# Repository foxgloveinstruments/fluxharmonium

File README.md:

# fluxharmonium
hardware and software for the fluxharmonium

## Hardware

Hardware design files for the primary electronics are located in the `kicad` of each primary function; [conductor](hardware/conductor/kicad), [ensemble](hardware/ensemble/kicad/), and [output](hardware/output/kicad).

## Software

The embedded microcontroller is currently a [Pimoroni Tiny2040 8MB](https://shop.pimoroni.com/products/tiny-2040) running CircuitPython. Firmware for the controller is located in the [src folder](src/)

Tested with Adafruit CircuitPython 8.0.5 on 2023-03-31; Pimoroni Tiny 2040 (8MB) with rp2040

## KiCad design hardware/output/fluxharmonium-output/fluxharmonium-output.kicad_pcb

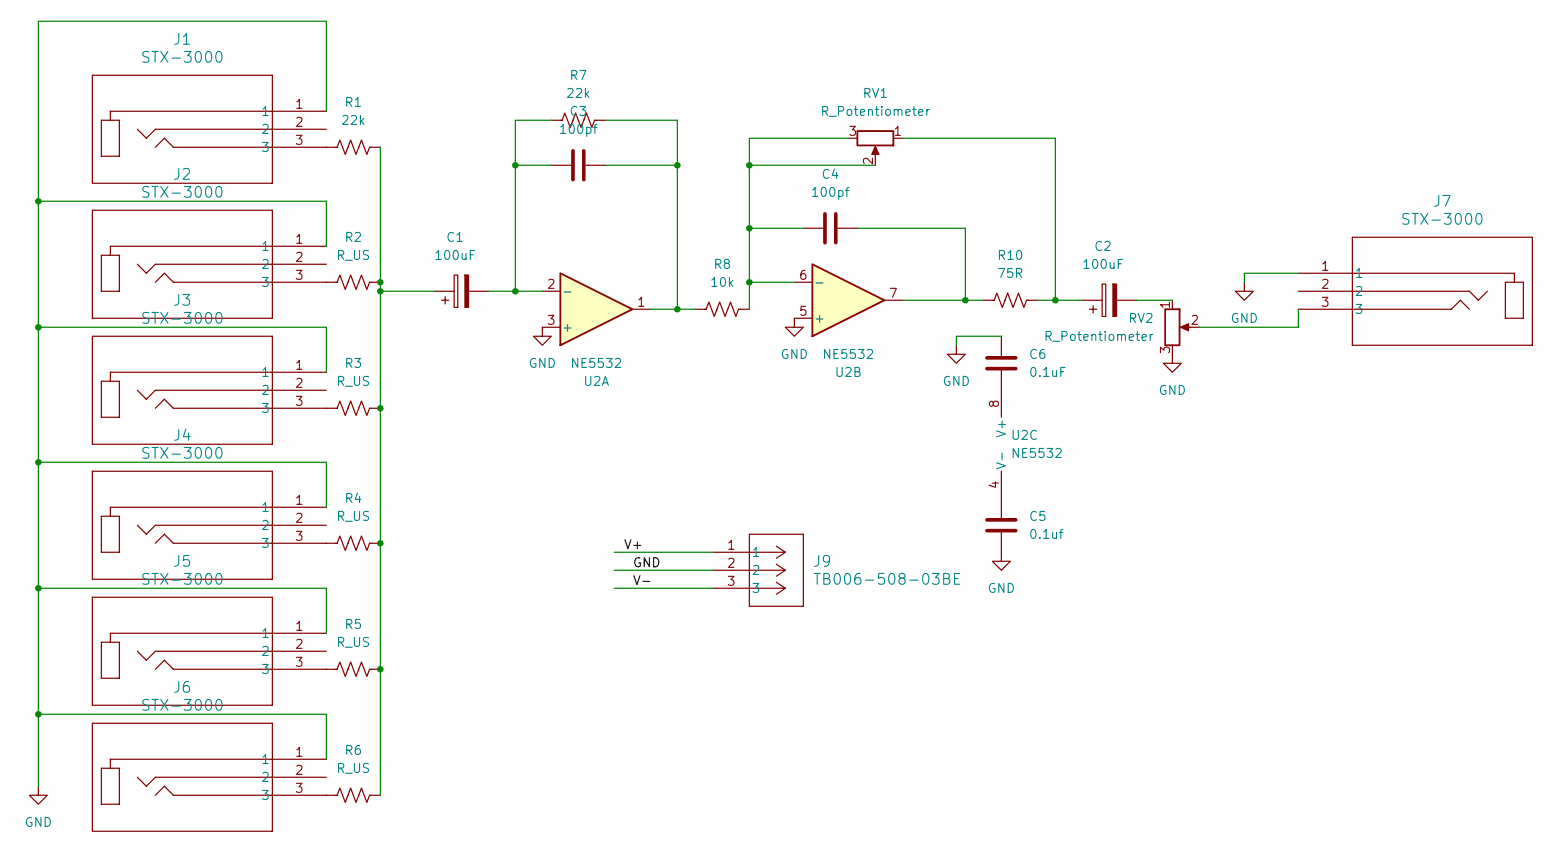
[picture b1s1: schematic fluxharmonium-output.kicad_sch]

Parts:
C1, C2: 100uF; CP_Radial_D5.0mm_P2.00mm
C3, C4: 100pf; C_Rect_L4.6mm_W2.0mm_P2.50mm_MKS02_FKP02
C5: 0.1uf; C_Disc_D3.8mm_W2.6mm_P2.50mm
C6: 0.1uF; C_Disc_D3.8mm_W2.6mm_P2.50mm
J1, J2, J3, J4, J5, J6, J7: STX-3000; STX-3000_KYC
J9: TB006-508-03BE; CONN3_TB006-508_CUD
R1, R7: 22k; R_Axial_DIN0207_L6.3mm_D2.5mm_P10.16mm_Horizontal
R2, R3, R4, R5, R6: R_US; R_Axial_DIN0207_L6.3mm_D2.5mm_P10.16mm_Horizontal
R8: 10k; R_Axial_DIN0207_L6.3mm_D2.5mm_P10.16mm_Horizontal
R10: 75R; R_Axial_DIN0207_L6.3mm_D2.5mm_P10.16mm_Horizontal
RV1: R_Potentiometer; Potentiometer_Bourns_3386P_Vertical
RV2: R_Potentiometer; PinSocket_1x03_P2.54mm_Vertical
U2: NE5532; DIP-8_W7.62mm

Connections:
/V+: J9.1
/V-: J9.3
GND: C5.1, C6.2, J1.1, J2.1, J3.1, J4.1, J5.1, J6.1, J7.1, J9.2, RV2.3, U2.3 (+), U2.5 (+)
unnamed: C1.1, R1.2, R2.2, R3.2, R4.2, R5.2, R6.2
unnamed: C2.1, R10.2, RV1.1
unnamed: C2.2, RV2.1
unnamed: C3.2, R7.2, R8.1, U2.1
unnamed: C4.2, R10.1, U2.7
unnamed: J1.3, R1.1
unnamed: J2.3, R2.1
unnamed: J3.3, R3.1
unnamed: J4.3, R4.1
unnamed: J5.3, R5.1
unnamed: J6.3, R6.1
unnamed: J7.3, RV2.2
unnamed: C1.2, C3.1, R7.1, U2.2 (-)
unnamed: C4.1, R8.2, RV1.2, RV1.3, U2.6 (-)
unnamed: C6.1, U2.8 (V+)
unnamed: C5.2, U2.4 (V-)

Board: 2 copper layers, 26 parts (0 on the bottom side), 17 nets, no tracks yet.

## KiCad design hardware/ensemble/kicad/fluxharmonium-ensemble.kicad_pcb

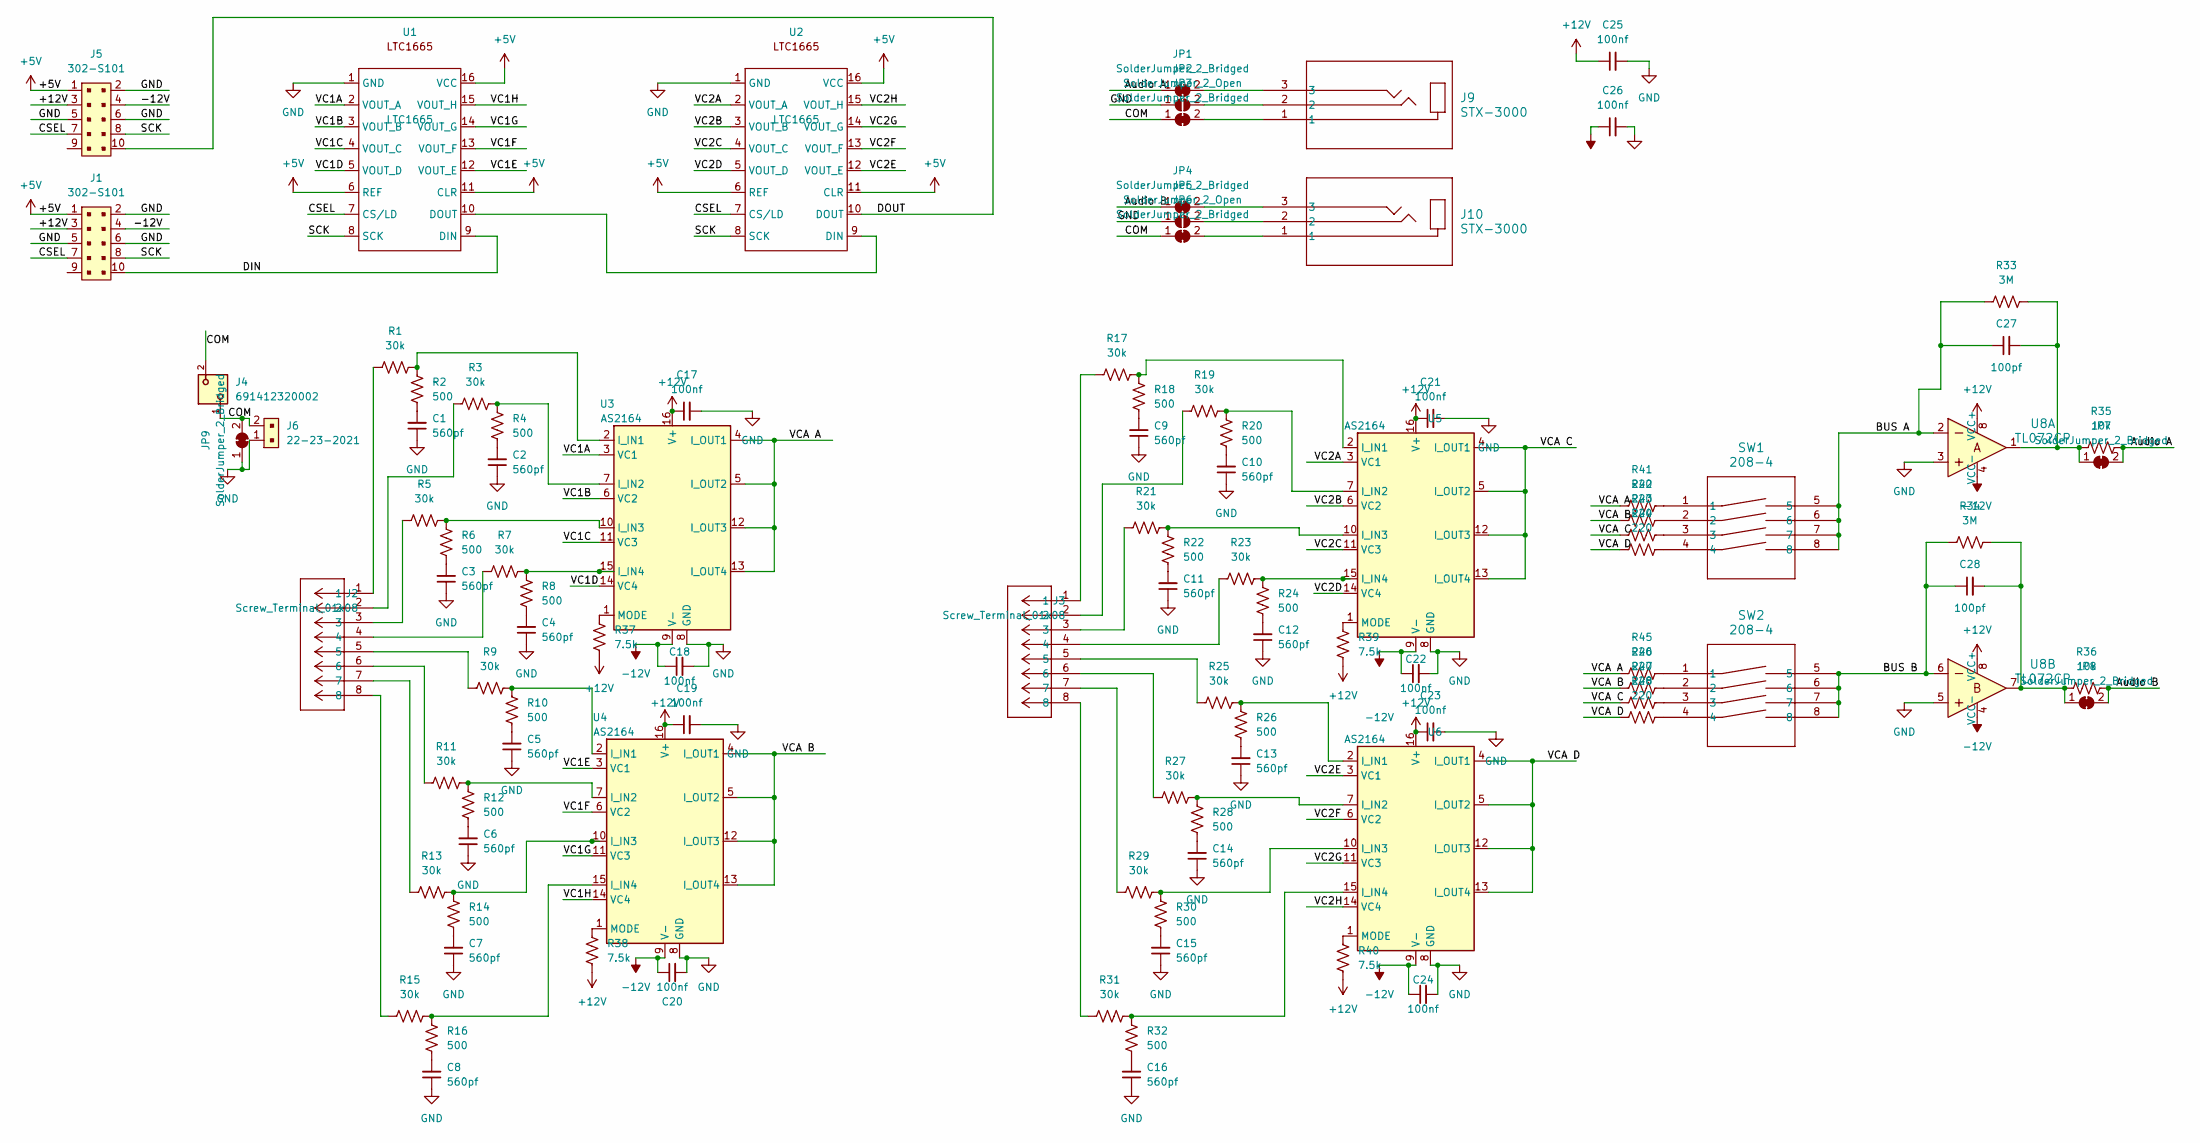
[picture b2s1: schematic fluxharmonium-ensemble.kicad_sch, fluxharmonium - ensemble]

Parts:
C1, C2, C3, C4, C5, C6, C7, C8, C9, C10, C11, C12, C13, C14, C15, C16: 560pf; C_Disc_D3.0mm_W2.0mm_P2.50mm
C17, C18, C19, C20, C21, C22, C23, C24, C25, C26: 100nf; C_Disc_D3.8mm_W2.6mm_P2.50mm
C27, C28: 100pf; C_Disc_D3.8mm_W2.6mm_P2.50mm
J1, J5: 302-S101; IDC-Header_2x05_P2.54mm_Latch_Vertical; MPN 302-S101; Digi-Key_PN ED1543-ND
J2, J3: Screw_Terminal_01x08; CONN_1755794_PXC
J4: 691412320002; PART-NUMBER 691412320002
J6: 22-23-2021; PinHeader_1x2_P2.54mm_Drill1.02mm; MPN 22-23-2021; Digi-Key_PN WM4200-ND
J9, J10: STX-3000; xess-STX-3000_KYC
JP1, JP3, JP4, JP6, JP7, JP8, JP9: SolderJumper_2_Bridged; SolderJumper-2_P1.3mm_Bridged_RoundedPad1.0x1.5mm
JP2, JP5: SolderJumper_2_Open; SolderJumper-2_P1.3mm_Open_RoundedPad1.0x1.5mm
R1, R3, R5, R7, R9, R11, R13, R15, R17, R19, R21, R23, R25, R27, R29, R31: 30k; R_Axial_DIN0207_L6.3mm_D2.5mm_P2.54mm_Vertical
R2, R4, R6, R8, R10, R12, R14, R16, R18, R20, R22, R24, R26, R28, R30, R32: 500; R_Axial_DIN0207_L6.3mm_D2.5mm_P2.54mm_Vertical
R33, R34: 3M; R_Axial_DIN0207_L6.3mm_D2.5mm_P2.54mm_Vertical
R35, R36: 10k; R_Axial_DIN0207_L6.3mm_D2.5mm_P2.54mm_Vertical
R37, R38, R39, R40: 7.5k; R_Axial_DIN0207_L6.3mm_D2.5mm_P2.54mm_Vertical
R41, R42, R43, R44, R45, R46, R47, R48: 220; R_Axial_DIN0207_L6.3mm_D2.5mm_P2.54mm_Vertical
SW1, SW2: 208-4; DIP8_208-4_CTS
U1, U2: LTC1665; DIP-16_W7.62mm_LongPads
U3, U4, U5, U6: AS2164; DIP-16_W7.62mm_LongPads
U8: TL072CP; DIP-8_W7.62mm; MPN TL072CP; Digi-Key_PN 296-1775-5-ND

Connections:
+5V: J1.1, J5.1, U1.6 (REF), U1.11 (CLR), U1.16 (VCC), U2.6 (REF), U2.11 (CLR), U2.16 (VCC)
+12V: C17.1, C19.1, C21.1, C23.1, C25.1, J1.3, J5.3, R37.1, R38.1, R39.1, R40.1, U3.16 (V+), U4.16 (V+), U5.16 (V+), U6.16 (V+), U8.8 (VCC+)
-12V: C18.1, C20.1, C22.1, C24.1, C26.1, J1.4, J5.4, U3.9 (V-), U4.9 (V-), U5.9 (V-), U6.9 (V-), U8.4 (VCC-)
/Audio A: JP1.1 (A), JP7.2 (B), R35.2
/Audio B: JP4.1 (A), JP8.2 (B), R36.2
/BUS A: C27.1, R33.1, SW1.5, SW1.6, SW1.7, SW1.8, U8.2
/BUS B: C28.1, R34.1, SW2.5, SW2.6, SW2.7, SW2.8, U8.6
/COM: J4.1, J4.2, J6.2, JP3.1 (A), JP6.1 (A), JP9.2 (B)
/CSEL: J1.7, J5.7, U1.7 (CS/LD), U2.7 (CS/LD)
/DIN: J1.10, U1.9 (DIN)
/DOUT: J5.10, U2.10 (DOUT)
/SCK: J1.8, J5.8, U1.8 (SCK), U2.8 (SCK)
/VC1A: U1.2 (VOUT_A), U3.3 (VC1)
/VC1B: U1.3 (VOUT_B), U3.6 (VC2)
/VC1C: U1.4 (VOUT_C), U3.11 (VC3)
/VC1D: U1.5 (VOUT_D), U3.14 (VC4)
/VC1E: U1.12 (VOUT_E), U4.3 (VC1)
/VC1F: U1.13 (VOUT_F), U4.6 (VC2)
/VC1G: U1.14 (VOUT_G), U4.11 (VC3)
/VC1H: U1.15 (VOUT_H), U4.14 (VC4)
/VC2A: U2.2 (VOUT_A), U5.3 (VC1)
/VC2B: U2.3 (VOUT_B), U5.6 (VC2)
/VC2C: U2.4 (VOUT_C), U5.11 (VC3)
/VC2D: U2.5 (VOUT_D), U5.14 (VC4)
/VC2E: U2.12 (VOUT_E), U6.3 (VC1)
/VC2F: U2.13 (VOUT_F), U6.6 (VC2)
/VC2G: U2.14 (VOUT_G), U6.11 (VC3)
/VC2H: U2.15 (VOUT_H), U6.14 (VC4)
/VCA A: R41.1, R45.1, U3.4 (I_OUT1), U3.5 (I_OUT2), U3.12 (I_OUT3), U3.13 (I_OUT4)
/VCA B: R42.1, R46.1, U4.4 (I_OUT1), U4.5 (I_OUT2), U4.12 (I_OUT3), U4.13 (I_OUT4)
/VCA C: R43.1, R47.1, U5.4 (I_OUT1), U5.5 (I_OUT2), U5.12 (I_OUT3), U5.13 (I_OUT4)
/VCA D: R44.1, R48.1, U6.4 (I_OUT1), U6.5 (I_OUT2), U6.12 (I_OUT3), U6.13 (I_OUT4)
GND: C1.1, C2.1, C3.1, C4.1, C5.1, C6.1, C7.1, C8.1, C9.1, C10.1, C11.1, C12.1, C13.1, C14.1, C15.1, C16.1, C17.2, C18.2, C19.2, C20.2, C21.2, C22.2, C23.2, C24.2, C25.2, C26.2, J1.2, J1.5, J1.6, J5.2, J5.5, J5.6, J6.1, JP2.1 (A), JP5.1 (A), JP9.1 (A), U1.1 (GND), U2.1 (GND), U3.8 (GND), U4.8 (GND), U5.8 (GND), U6.8 (GND), U8.3, U8.5
unnamed: C1.2, R2.1
unnamed: C2.2, R4.1
unnamed: C3.2, R6.1
unnamed: C4.2, R8.1
unnamed: C5.2, R10.1
unnamed: C6.2, R12.1
unnamed: C7.2, R14.1
unnamed: C8.2, R16.1
unnamed: C9.2, R18.1
unnamed: C10.2, R20.1
unnamed: C11.2, R22.1
unnamed: C12.2, R24.1
unnamed: C13.2, R26.1
unnamed: C14.2, R28.1
unnamed: C15.2, R30.1
unnamed: C16.2, R32.1
unnamed: J2.1, R1.1
unnamed: J2.2, R3.1
unnamed: J2.3, R5.1
unnamed: J2.4, R7.1
unnamed: J2.5, R9.1
unnamed: J2.6, R11.1
unnamed: J2.7, R13.1
unnamed: J2.8, R15.1
unnamed: J3.1, R17.1
unnamed: J3.2, R19.1
unnamed: J3.3, R21.1
unnamed: J3.4, R23.1
unnamed: J3.5, R25.1
unnamed: J3.6, R27.1
unnamed: J3.7, R29.1
unnamed: J3.8, R31.1
unnamed: J9.3, JP1.2 (B)
unnamed: J9.2, JP2.2 (B)
unnamed: J9.1, JP3.2 (B)
unnamed: J10.3, JP4.2 (B)
unnamed: J10.2, JP5.2 (B)
unnamed: J10.1, JP6.2 (B)
unnamed: C27.2, JP7.1 (A), R33.2, R35.1, U8.1
unnamed: C28.2, JP8.1 (A), R34.2, R36.1, U8.7
unnamed: R41.2, SW1.1
unnamed: R42.2, SW1.2
unnamed: R43.2, SW1.3
unnamed: R44.2, SW1.4
unnamed: R45.2, SW2.1
unnamed: R46.2, SW2.2
unnamed: R47.2, SW2.3
unnamed: R48.2, SW2.4
unnamed: U1.10 (DOUT), U2.9 (DIN)
unnamed: R1.2, R2.2, U3.2 (I_IN1)
unnamed: R3.2, R4.2, U3.7 (I_IN2)
unnamed: R5.2, R6.2, U3.10 (I_IN3)
unnamed: R7.2, R8.2, U3.15 (I_IN4)
unnamed: R37.2, U3.1 (MODE)
unnamed: R9.2, R10.2, U4.2 (I_IN1)
unnamed: R11.2, R12.2, U4.7 (I_IN2)
unnamed: R13.2, R14.2, U4.10 (I_IN3)
unnamed: R15.2, R16.2, U4.15 (I_IN4)
unnamed: R38.2, U4.1 (MODE)
unnamed: R17.2, R18.2, U5.2 (I_IN1)
unnamed: R19.2, R20.2, U5.7 (I_IN2)
unnamed: R21.2, R22.2, U5.10 (I_IN3)
unnamed: R23.2, R24.2, U5.15 (I_IN4)
unnamed: R39.2, U5.1 (MODE)
unnamed: R25.2, R26.2, U6.2 (I_IN1)
unnamed: R27.2, R28.2, U6.7 (I_IN2)
unnamed: R29.2, R30.2, U6.10 (I_IN3)
unnamed: R31.2, R32.2, U6.15 (I_IN4)
unnamed: R40.2, U6.1 (MODE)

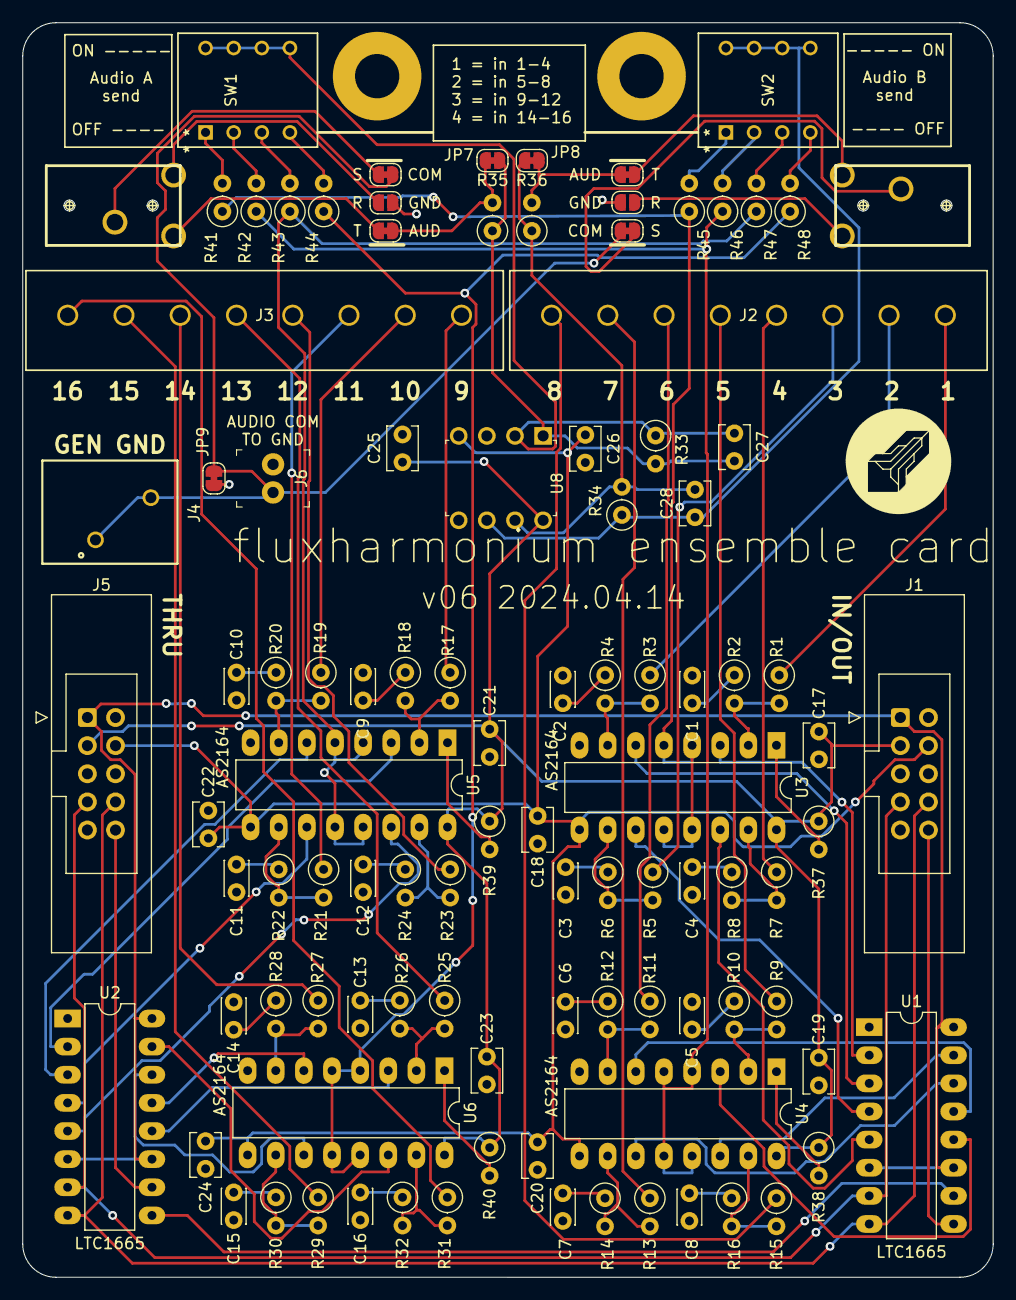
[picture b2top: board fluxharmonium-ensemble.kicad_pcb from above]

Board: 2 copper layers, 87.6 x 113.3 mm, 104 parts (0 on the bottom side), 102 nets.

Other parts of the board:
Hole1, Hole2: MountingHole_4mm_Pad

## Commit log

2024-04-21 Added v6 hardware and firmware
2024-05-13 Create fluxharmonium.py
    Skeleton for RPI MIDI processor
2024-05-20 Split to various versions for different hardware
2024-05-20 Updated working pisound version.
2024-06-02 Updated and working tiny2040 version. Other platform WIP.
